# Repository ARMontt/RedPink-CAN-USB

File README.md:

# RedPink-CAN-USB

Mini PCB for STM32C09, useful for general purposes that involves mostly communication through a CANBUS to USB. This board helps to simplify development of industrial devices that requires CANBUS communication. 

## Motivation

Nowadays there are many CAN-USB or CAN-UART devices, that require external coding (usually in C) to test the communication, however, a more user-friendly interface accompanied by a simple CAN-USB device would improve the performance for developing new industrial devices.

## Interactive BOM Viewer

Please feel free to check the Layout and BOM in the following URL: https://armontt.github.io/RedPink-CAN-USB/ibom.html

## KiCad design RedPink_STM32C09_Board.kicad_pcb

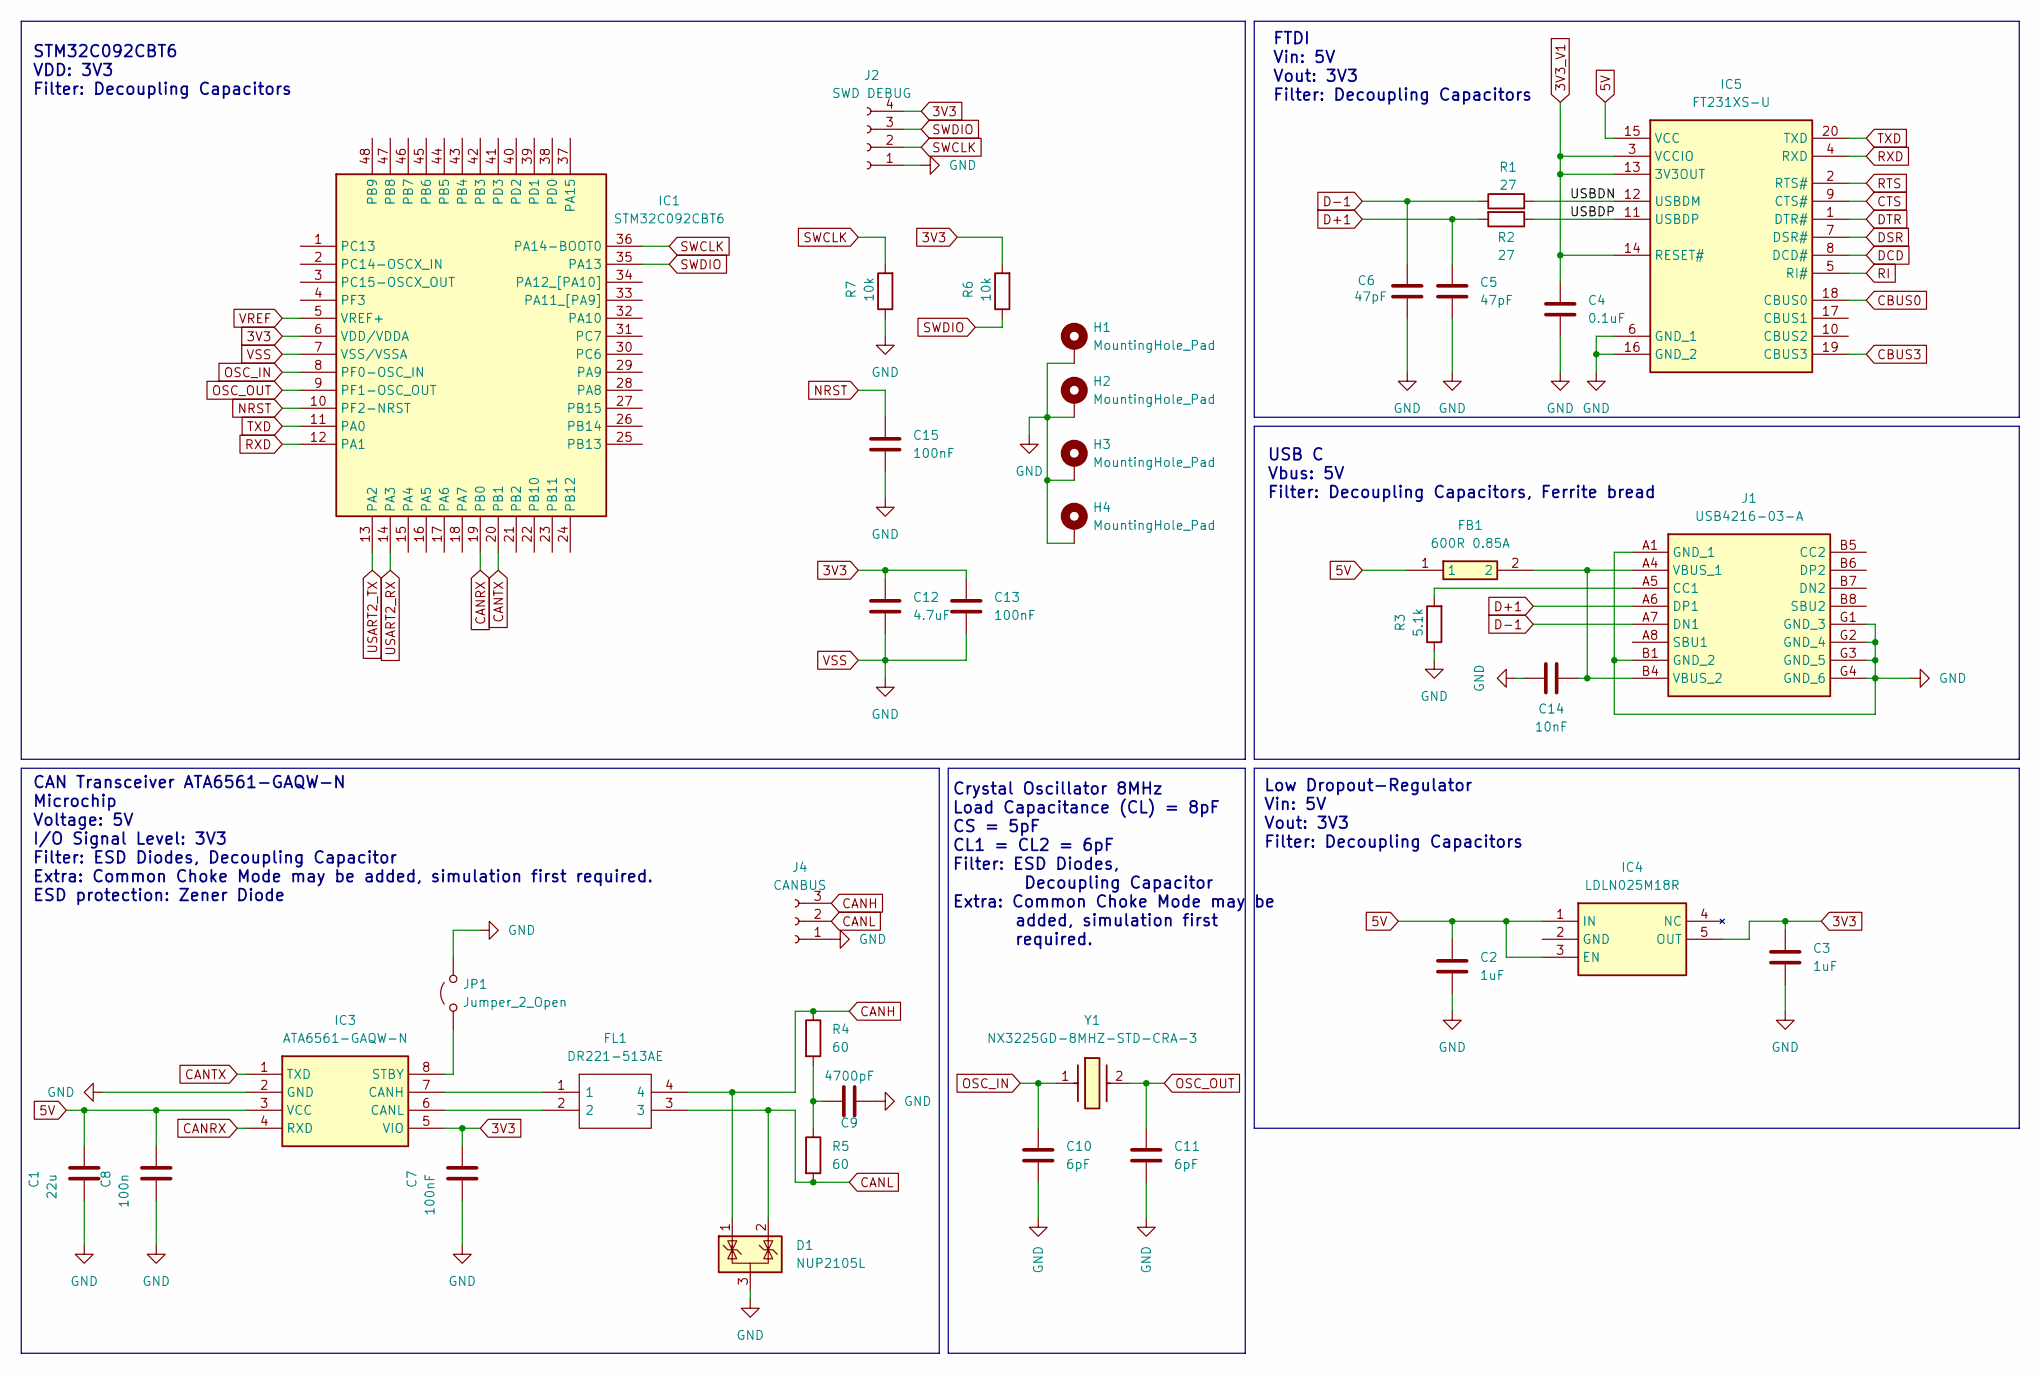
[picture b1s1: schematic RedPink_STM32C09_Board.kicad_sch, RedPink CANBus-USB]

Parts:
C1: 22u; C_0603_1608Metric_Pad1.08x0.95mm_HandSolder
C2, C3: 1uF; C_0603_1608Metric_Pad1.08x0.95mm_HandSolder
C4: 0.1uF; C_0603_1608Metric_Pad1.08x0.95mm_HandSolder
C5, C6: 47pF; C_0603_1608Metric_Pad1.08x0.95mm_HandSolder
C7, C13, C15: 100nF; C_0603_1608Metric_Pad1.08x0.95mm_HandSolder
C8: 100n; C_0603_1608Metric_Pad1.08x0.95mm_HandSolder
C9: 4700pF; C_0603_1608Metric_Pad1.08x0.95mm_HandSolder
C10, C11: 6pF; C_0603_1608Metric_Pad1.08x0.95mm_HandSolder
C12: 4.7uF; C_0603_1608Metric_Pad1.08x0.95mm_HandSolder
C14: 10nF; C_0603_1608Metric_Pad1.08x0.95mm_HandSolder
D1: NUP2105L; SOT-23
FB1: 600R 0.85A; BLM18SP221SN1B; Mouser Part Number 81-BLM18HE601SN1D
FL1: DR221-513AE; DR221474AE; Mouser Part Number 652-DR221-513AE
H1, H2, H3, H4: MountingHole_Pad; MountingHole_2.5mm_Pad
IC1: STM32C092CBT6; QFP50P900X900X160-48N; Manufacturer_Part_Number STM32C092CBT6
IC3: ATA6561-GAQW-N; CANBUS SOIC127P600X175-8N; Mouser Part Number 579-ATA6561-GAQW-N
IC4: LDLN025M18R; LDO SOT95P280X145-5N; Mouser Part Number 511-LDLN025M18R
IC5: FT231XS-U; FTDI SOP64P599X175-20N; Mouser Part Number 895-FT231XS-U
J1: USB4216-03-A; USB421603A; Mouser Part Number 640-USB4216-03-A
J2: SWD DEBUG; PinHeader_1x04_P2.54mm_Vertical
J4: CANBUS; PinHeader_1x03_P2.54mm_Vertical
JP1: Jumper_2_Open; SolderJumper-2_P1.3mm_Open_RoundedPad1.0x1.5mm
R1, R2: 27; R_0603_1608Metric_Pad0.98x0.95mm_HandSolder
R3: 5.1k; R_0603_1608Metric_Pad0.98x0.95mm_HandSolder
R4, R5: 60; R_0603_1608Metric_Pad0.98x0.95mm_HandSolder
R6, R7: 10k; R_0603_1608Metric_Pad0.98x0.95mm_HandSolder
Y1: NX3225GD-8MHZ-STD-CRA-3; NX3225GD8MHZSTDCRA3; Mouser Part Number 344-NX3225GD8MCRA3

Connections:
3V3: C3.1, C7.2, C12.1, C13.1, IC1.6 (VDD/VDDA), IC3.5 (VIO), IC4.5 (OUT), J2.4, R6.2
3V3_V1: C4.1, IC5.3 (VCCIO), IC5.13 (3V3OUT), IC5.14 (RESET#)
5V: C1.2, C2.1, C8.2, FB1.1, IC3.3 (VCC), IC4.1 (IN), IC4.3 (EN), IC5.15 (VCC)
/USBDN: IC5.12 (USBDM), R1.2
/USBDP: IC5.11 (USBDP), R2.1
CANH: D1.1 (K), FL1.4, J4.3, R4.1
CANL: D1.2 (K), FL1.3, J4.2, R5.2
CANRX: IC1.19 (PB0), IC3.4 (RXD)
CANTX: IC1.20 (PB1), IC3.1 (TXD)
CBUS0: IC5.18 (CBUS0)
CBUS3: IC5.19 (CBUS3)
CTS: IC5.9 (CTS#)
D+1: C5.1, J1.A6 (DP1), R2.2
D-1: C6.1, J1.A7 (DN1), R1.1
DCD: IC5.8 (DCD#)
DSR: IC5.7 (DSR#)
DTR: IC5.1 (DTR#)
NRST: C15.1, IC1.10 (PF2-NRST)
unnamed: C9.1, R4.2, R5.1
unnamed: FL1.1, IC3.7 (CANH)
unnamed: FL1.2, IC3.6 (CANL)
unnamed: IC3.8 (STBY), JP1.1 (A)
unnamed: J1.A5 (CC1), R3.2
unnamed: C14.2, FB1.2, J1.A4 (VBUS_1), J1.B4 (VBUS_2)
OSC_IN: C10.1, IC1.8 (PF0-OSC_IN), Y1.1
OSC_OUT: C11.1, IC1.9 (PF1-OSC_OUT), Y1.2
RI: IC5.5 (RI#)
RTS: IC5.2 (RTS#)
RXD: IC1.12 (PA1), IC5.4 (RXD)
SWCLK: IC1.36 (PA14-BOOT0), J2.2, R7.2
SWDIO: IC1.35 (PA13), J2.3, R6.1
TXD: IC1.11 (PA0), IC5.20 (TXD)
USART2_RX: IC1.14 (PA3)
USART2_TX: IC1.13 (PA2)
VREF: IC1.5 (VREF+)
VSS: C1.1, C2.2, C3.2, C4.2, C5.2, C6.2, C7.1, C8.1, C9.2, C10.2, C11.2, C12.2, C13.2, C14.1, C15.2, D1.3 (A), H1.1, H2.1, H3.1, H4.1, IC1.7 (VSS/VSSA), IC3.2 (GND), IC5.6 (GND_1), IC5.16 (GND_2), J1.A1 (GND_1), J1.B1 (GND_2), J1.G1 (GND_3), J1.G2 (GND_4), J1.G3 (GND_5), J1.G4 (GND_6), J2.1, J4.1, JP1.2 (B), R3.1, R7.1

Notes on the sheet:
STM32C092CBT6 VDD: 3V3 Filter: Decoupling Capacitors
Crystal Oscillator 8MHz Load Capacitance (CL) = 8pF CS = 5pF CL1 = CL2 = 6pF Filter: ESD Diodes, Decoupling Capacitor Extra: Common Choke Mode may be added, simulation first required.
CAN Transceiver ATA6561-GAQW-N Microchip Voltage: 5V I/O Signal Level: 3V3 Filter: ESD Diodes, Decoupling Capacitor Extra: Common Choke Mode may be added, simulation first required. ESD protection: Zener Diode
Low Dropout-Regulator Vin: 5V Vout: 3V3 Filter: Decoupling Capacitors
FTDI Vin: 5V Vout: 3V3 Filter: Decoupling Capacitors
USB C Vbus: 5V Filter: Decoupling Capacitors, Ferrite bread

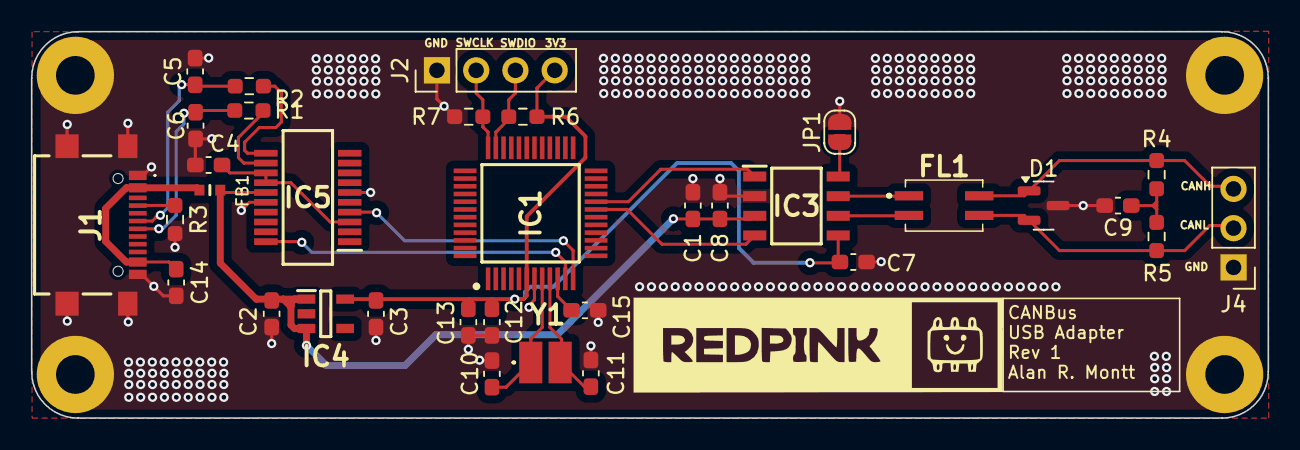
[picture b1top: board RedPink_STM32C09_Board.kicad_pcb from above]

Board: 2 copper layers, 80.0 x 25.0 mm, 38 parts (0 on the bottom side), 25 nets.

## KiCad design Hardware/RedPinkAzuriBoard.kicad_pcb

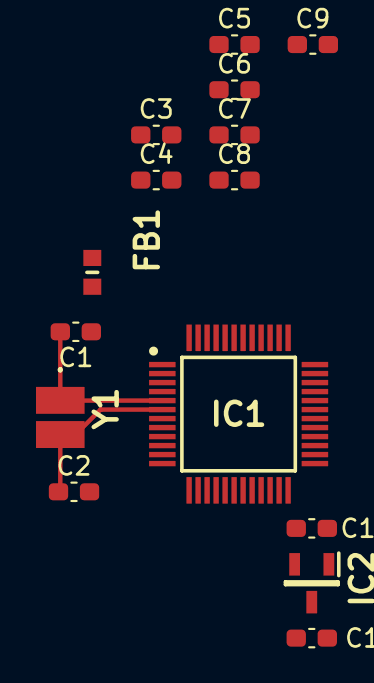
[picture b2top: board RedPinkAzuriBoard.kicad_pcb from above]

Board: 2 copper layers, 15 parts (0 on the bottom side), 7 nets.

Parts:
C1, C2: 8.2pF; C_0603_1608Metric_Pad1.08x0.95mm_HandSolder
C3, C4, C5, C6: 100nF; C_0603_1608Metric_Pad1.08x0.95mm_HandSolder
C7: 4.7uF; C_0603_1608Metric_Pad1.08x0.95mm_HandSolder
C8: 10nF; C_0603_1608Metric_Pad1.08x0.95mm_HandSolder
C9, C18, C19: 1uF; C_0603_1608Metric_Pad1.08x0.95mm_HandSolder
FB1: BBNQ00160808601Y00; BEADC1608X95N
IC1: STM32L431CBT6
IC2: TPS7A0533PDBZR; SOT95P237X112-3N
Y1: 8MHz NX3225GD; NX3225GD8MHZSTDCRA3

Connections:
3V3: C19.2, FB1.1, IC1.24 (VDD_1), IC1.48 (VDD_2), IC2.2 (OUT)
3V3A: C8.1, C9.1, FB1.2, IC1.9 (VDDA/VREF+)
5V: C18.2, IC2.3 (IN)
+3V3: C3.1, C4.1, C5.1, C6.1, C7.1
GND: C1.1, C2.2, C3.2, C4.2, C5.2, C6.2, C7.2, C8.2, C9.2, C18.1, C19.1, IC1.8 (VSSA/VREF-), IC1.23 (VSS_1), IC1.35 (VSS_2), IC1.47 (VSS_3), IC2.1 (GND)
PH0: C1.2, IC1.5 (PH0-OSC_IN_(PH0)), Y1.1
PH1: C2.1, IC1.6 (PH1-OSC_OUT_(PH1)), Y1.2

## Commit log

2025-03-06 Files created
2025-08-09 New version of RedPink Board
    Replaced STM32L4 design, changed to STM32C09
2026-01-13 Updated design - focus on CAN-USB Application
2026-02-18 Updated PCB layout, output connector replaced
    1) Removed 5V pin from output pin header
    2) Added round corners
    3) Replace pin header output
2026-02-18 Interactive BOM Added
2026-02-18 Add Interactive BOM Viewer section to README
    Added section for Interactive BOM Viewer with URL.
